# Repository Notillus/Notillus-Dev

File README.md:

Notillus
========

Repositorio de desarrollo de la Notillus, impresora originalmente inspirada en la Tantillus de https://github.com/Intrinsically-Sublime/Tantillus por su tamaño y portabilidad.

La Notillus ahora lleva el tanga extruder de coleta http://www.thingiverse.com/thing:742584

Los archivos de desarrollo de la Tantillus-Mks ahora estan en: 
https://github.com/darkjavi/Tantillus-MKS

Usando git:

Instrucciones para linux:

-Instalar:

	sudo apt-get install git

-Configurar

	git config --global user.name "TuNombre"

	git config --global user.email "tu@email.com"

-Primer clonado del repo:

	cd carpeta/donde/quieres/descargar

	git clone https://github.com/darkjavi/Notillus.git

-Actualizando el repo:

	cd carpeta/del/repo

	git pull

-Despues de haber modificado cosas en los ficheros:

	cd carpeta/del/repo

	git add .       (añade todos los archivos nuevos)

	git commit -a	(se abrira una ventana en la que obligatoriamente hay que escribir algo sobre los cambios hechos)

	git push origin (manda los cambios de vuelta a github, pedira nombre de usuario/pass)

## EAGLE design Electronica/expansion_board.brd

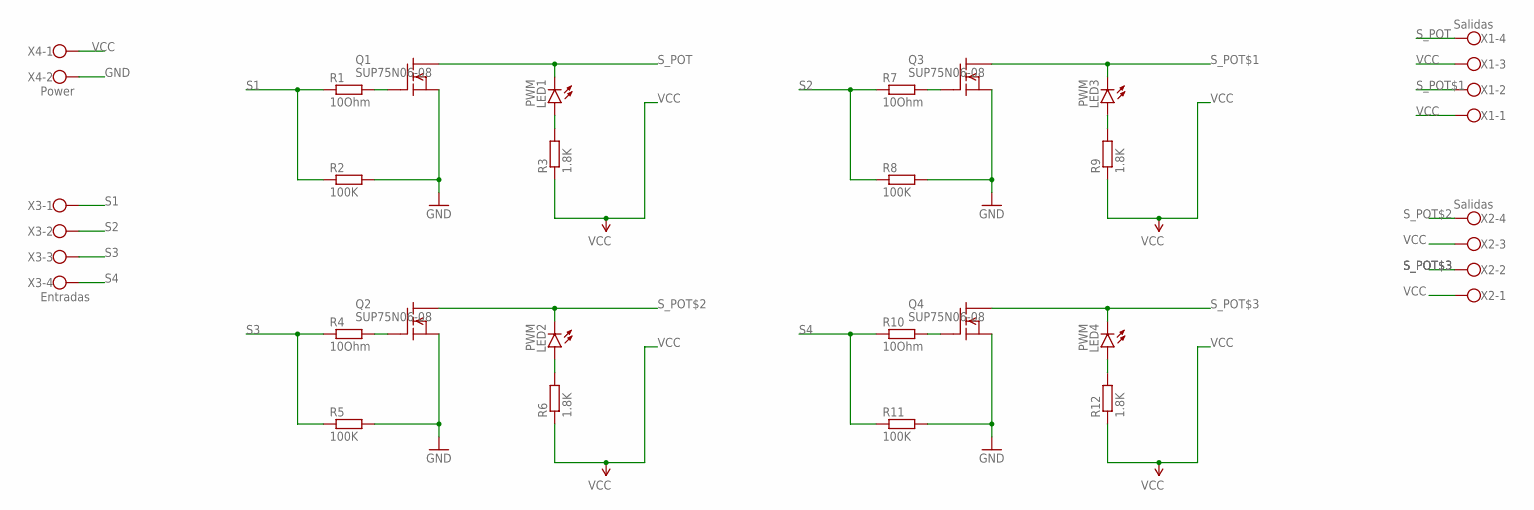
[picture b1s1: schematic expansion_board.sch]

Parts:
LED1, LED2, LED3, LED4: PWM; LED5MM
Q1, Q2, Q3, Q4: SUP75N06-08; TO220
R1, R4, R7, R10: 10Ohm; 0207/7
R2, R5, R8, R11: 100K; 0207/7
R3, R6, R9, R12: 1.8K; 0207/7
X1, X2: Salidas; W237-4
X3: Entradas; W237-4
X4: Power; W237-102

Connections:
GND: Q1.3 (S), Q2.3 (S), Q3.3 (S), Q4.3 (S), R2.2, R5.2, R8.2, R11.2, X4.2
unnamed: Q3.1 (G), R7.2
unnamed: Q1.1 (G), R1.2
unnamed: Q2.1 (G), R4.2
unnamed: LED1.A, R3.2
unnamed: LED2.A, R6.2
unnamed: LED3.A, R9.2
unnamed: Q4.1 (G), R10.2
unnamed: LED4.A, R12.2
S1: R1.1, R2.1, X3.1
S2: R7.1, R8.1, X3.2
S3: R4.1, R5.1, X3.3
S4: R10.1, R11.1, X3.4
S_POT: LED1.K (C), Q1.2 (D), X1.4
S_POT$1: LED3.K (C), Q3.2 (D), X1.2
S_POT$2: LED2.K (C), Q2.2 (D), X2.4
S_POT$3: LED4.K (C), Q4.2 (D), X2.2
VCC: R3.1, R6.1, R9.1, R12.1, X1.1, X1.3, X2.1, X2.3, X4.1

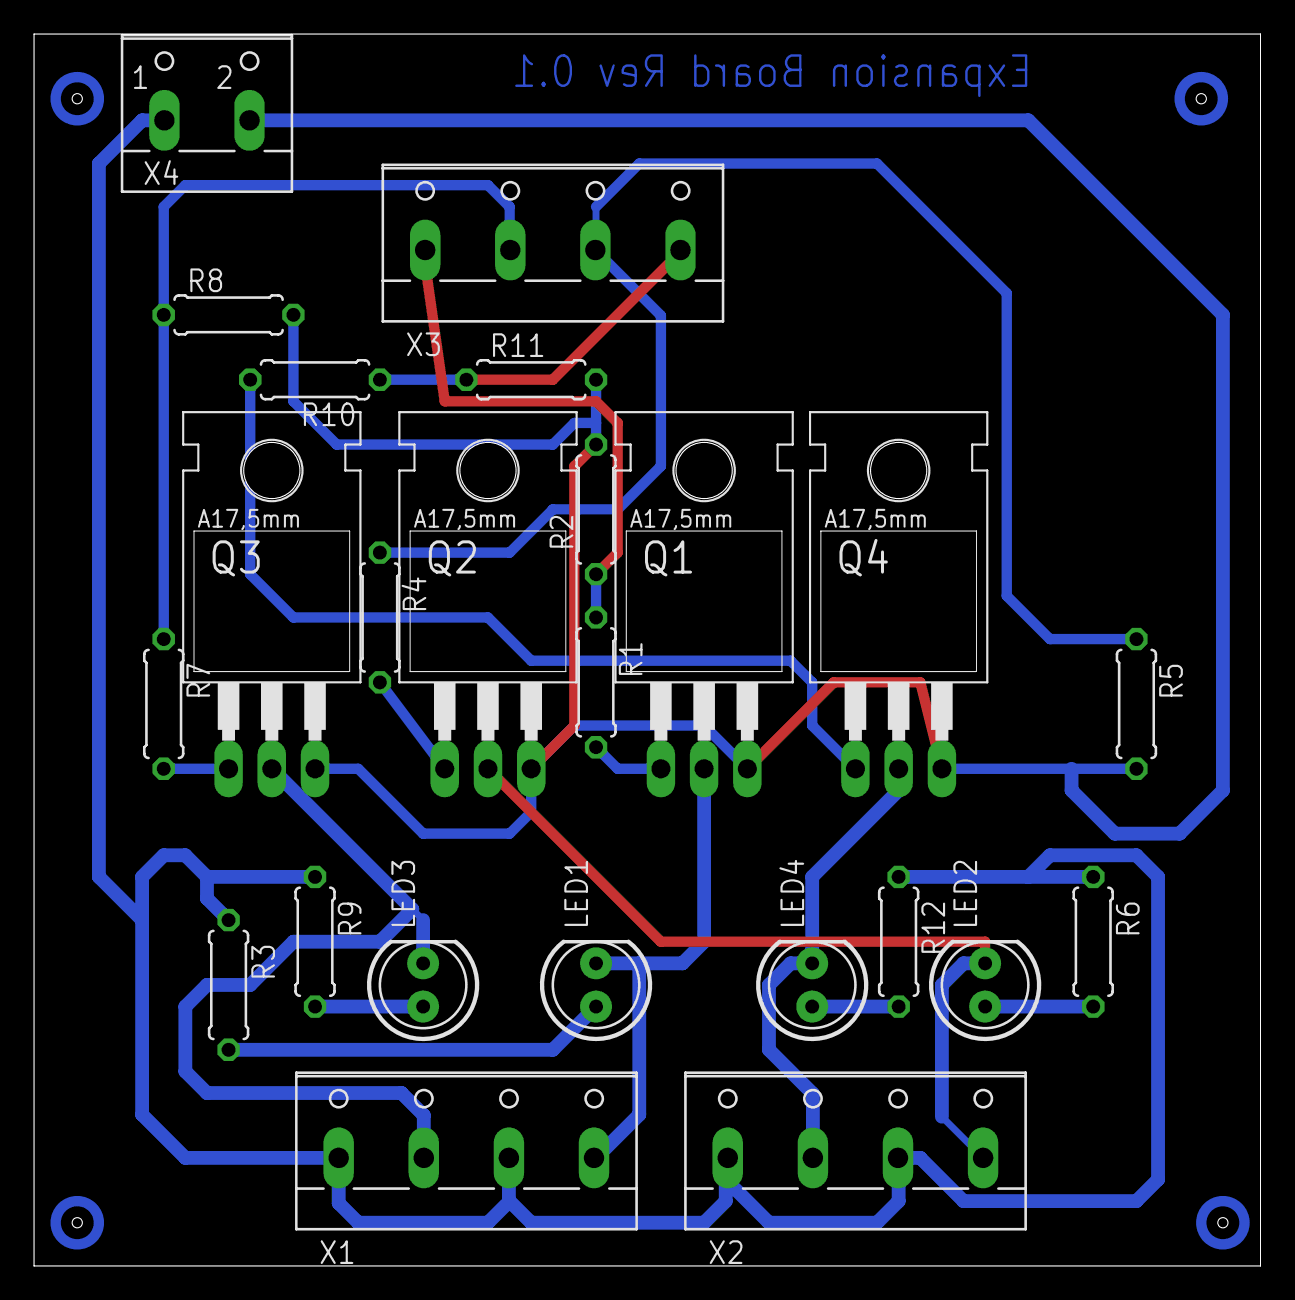
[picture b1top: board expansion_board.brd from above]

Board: 2 copper layers, 72.1 x 72.4 mm, 24 parts (0 on the bottom side), 18 nets.

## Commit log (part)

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2014-06-22 Añadida carpeta Electronica a Piezas Enrique y añadidas piezas caja electronica
2014-06-22 Creación carpeta EjeZ
2014-06-27 Primer commit. Añadidos todos los ficheros de mi portatil
2014-06-28 Añadidas instrucciones basicas para usar git desde la consola.
    Changes to be committed:
    modified: README.md
2014-06-28 Lista de piezas del eje Z
2014-06-29 modified: Notillus-coreXY/CorteLaser/LEEME.txt
2014-06-30 Versión alpha del chasis. Sin agujeros de anclaje ¡Las medidas del display hay que contrastarlas!
2014-07-24 Añadidos firmwares para tantillus original y version mks-moebyus
2014-07-31 Nuevo y mejorado barrilete para el hilo. 88 pasos por mm Firmware configurado para la version rslot de hilo con barilletes
    Changes to be committed:
    modified: Kit-TantillusMks-TSLOT/Extras/spectra-reel-m8-v2.stl
    modified: Kit-TantillusMks-TSLOT/Firmware/Marlin-tantillus-Moebyus/Marlin/Configuration.h
    modified: Piezas-Javi/Tantillus/spectra-reel-8mm-smaller2.fcstd
    renamed: Piezas-Javi/Tantillus/spectra-reel-8mm-smaller2.fcstd -> Piezas-Javi/Tantillus/spectra-reel-8mm-smaller2.fcstd1
2014-08-05 version 0.8 del soporte de filamento para la TSLOT new file: Piezas-Javi/Tantillus/soporte-filamento-pieza2.fcstd new file: Piezas-Javi/Tantillus/soporte-filamento-pieza2.fcstd1 new file: Piezas-Javi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
2014-08-08 Añadidos los soportes para los Nema de los ejes
2014-08-09 Empezados los esquinazos y las piezas de cruce del hilo
    new file: Piezas-Javi/Notillus/corexy-cruce-alineado.fcstd
    new file: Piezas-Javi/Notillus/esquina.fcstd
2014-08-11 Piezas del coreXY, falta ajustar la medida de las poleas del hilo
    new file: Piezas-Javi/Notillus/coreXY-carroY.fcstd
    new file: Piezas-Javi/Notillus/coreXY-frontal.fcstd
    new file: Piezas-Javi/Notillus/coreXY-trasera.fcstd
2014-08-12 Esquinas superioes listas para imprimir
2014-08-14 Reordenada la carpeta de Notillus
2014-08-16 new file: Notillus-coreXY/STL/esquinas-superiores.stl modified: Piezas-Javi/Notillus/esquina-superior.fcstd modified: Piezas-Javi/Notillus/esquina-superior.fcstd1 new file: Piezas-Javi/Notillus/esqui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
2014-08-16 Preliminar de la esquina inferior
    new file: Piezas-Javi/Notillus/esquina-inferior.fcstd
2014-08-16 Añadido frontal para el display Añadido rueda para el encoder del display Prototipo del cajon para electronica [¡COMPROBAR MEDIDAS!]
2014-08-16 Primera version de la pieza corexy-trasera. Imprime bien, aunque el final del carrera le queda un poco justo
    new file: Notillus-coreXY/XY/corexy-trasera.stl
2014-08-19 Modificada la ubicación del Slot SD
2014-08-19 ESquina inferior v1
2014-08-20 Nuevo molde para hacer las patas de silicona new file: Notillus-coreXY/Estructura/molde-patas.stl new file: Piezas-Javi/Tantillus/Molde-patas.fcstd
2014-08-21 carro x : pieza empezada soporte de motor achaflanado , tiempo estimado de impresion 1:45 new file: Piezas-Javi/Notillus/coreXY-carroX.fcstd new file: Piezas-Nano/soporte-Nema_v2-achaflanado.fcstd
2014-08-21 Modificada la guia de hilo
2014-08-22 Barrilete para el motor
2014-08-23 prototipo de tensor de hilo
2014-08-25 Barrilete optimizado para 100ppmm
2014-08-27 Soporte display adelgazado
2014-08-27 gcodes del display
2014-08-28 Barriletede hilo optimizado
2014-09-01 Mejora de los rieles del cajon
2014-09-02 Barriletes modificados Soporte para ventilador de capa Rieles de cajon [SIN MEDIDAS REALES]
2014-09-03 Nuevo Eje Z en progreso new file: Piezas-Javi/nuevo-z/plataforma.fcstd
2014-09-05 Cajon modificado [SIN TERMINAR]
2014-09-06 Enredando con el firmware para activar el ventilador de capa y cambiar el logo/textos de la pantalla de inicio. en add --all se han metido algunos ficheros antiguos que supongo que no se habian añadi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
2014-09-06 new file: Piezas-Javi/nuevo-z/z-completo-V2.fcstd
2014-09-06 Cajon de electronica 2.0
2014-09-07 Extrusor v0.8 new file: Piezas-Javi/Notillus/extrusor.fcstd
2014-09-07 añadido el extrusor al ensamblaje modified: Piezas-Javi/Notillus/Ensamblaje.fcstd
2014-09-07 Pequeños ajustes post-impresion modified: Notillus-coreXY/Extrusor/cuerpo-ext1.stl modified: Notillus-coreXY/Extrusor/cuerpo.stl modified: Piezas-Javi/Notillus/extrusor.fcstd
2014-09-08 Soporte motor Nema reducido
2014-09-10 Cajon de electronica achaflanado
2014-09-22 Trabajos en el eje Z modified: Piezas-Javi/nuevo-z/z-completo-V2.fcstd modified: Piezas-Javi/nuevo-z/z-completo-V2.fcstd1
2014-09-23 Tantillus mks: Invertido el Eje Y en el firmware, hay que invertir tambien el cable del motor
2014-09-26 Compartimento para repuestos y herramientas
2014-09-27 Soporte para imanes de 12mm
2014-09-27 Nuevo soporte para los motores
2014-09-27 Soportes para inclinar el Display
2014-09-29 Soporte motor rectificado.
2014-09-30 Soporte para filamento con tolerancias reparadas
2014-10-04 Idea de soporte de motor y doble barrilete para la traccion
    new file: Piezas-Javi/Notillus/soporte-motorv4.fcstd
2014-10-09 Mas trabajos en el Z modified: Piezas-Javi/nuevo-z/z-completo-V2.fcstd
2014-10-14 EjeZ 2.0 listo modified: Piezas-Javi/nuevo-z/z-completo-V2.fcstd modified: Piezas-Javi/nuevo-z/z-completo-V2.fcstd1
2014-10-15 new file: Piezas-Javi/Notillus/Carcasa/piezabase25x30.fcstd
2014-10-16 Avances en el soporte motor Nuevo ensamblaje para facilitar el diseño de la carcasa new file: Piezas-Javi/Notillus/Carcasa-Ensamblaje.fcstd modified: Piezas-Javi/Notillus/Carcasa/piezabase25x30.fcstd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
2014-10-21 Nueva esquina inferior un poco mas pequeña y con tornilleria M4 Agregada al ensamblaje modificado: Piezas-Javi/Notillus/Carcasa-Ensamblaje.fcstd new file: Piezas-Javi/Notillus/v2/esquina-inferior.fcs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
2014-10-22 new file: Notillus-coreXY/MotoresXY/barriteleV5.stl modificado: Piezas-Javi/Notillus/Carcasa-Ensamblaje.fcstd
2014-10-26 Nuevo trinquete para tensar el hilo en el carro. modified: Piezas-Javi/Notillus/v2/coreXY2.fcstd new file: Piezas-Javi/Notillus/v2/knob-trinquete.fcstd
2014-10-27 modified: Piezas-Javi/Notillus/v2/coreXY2.fcstd
2014-11-01 Version 2 del Compartimento de herramientas
2014-11-03 Soporte motor completado new file: Notillus-coreXY/MotoresXY/SoporteMotorV4.stl new file: Notillus-coreXY/MotoresXY/barriteleSecundarioV5.stl new file: Notillus-coreXY/MotoresXY/barriteleTractorV5.st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
2014-11-04 Cajón para la electronica
2014-11-05 Añadido el nuevo soporte display al ensamblaje modificado: Piezas-Javi/Notillus/Carcasa-Ensamblaje.fcstd
2014-11-13 Revisado enganche de cajon y display
2014-11-15 Barriletes 5.2 un poco mas grandes. Generados gcodes extralentos new file: Notillus-coreXY/MotoresXY/GCODE/barriteles-ABS-INSTAL-MEGATRON.gcode new file: Notillus-coreXY/MotoresXY/GCODE/barriteles-AB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
2014-11-29 new file: Notillus-coreXY/MotoresXY/barriteleSecundarioV5.2.stl new file: Notillus-coreXY/MotoresXY/barriteleTractorV5.2.stl modified: Piezas-Javi/Notillus/v2/coreXY2.fcstd modified: Piezas-Javi/Noti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
2014-11-30 Z retocado. Se acerca el conjunto a la pared 8mm para evitar colisiones con el hotend.
    modificado: Notillus-coreXY/Z2.0/z_idler.stl
    modificado: Notillus-coreXY/Z2.0/z_motor.stl
    modificado: Piezas-Javi/Notillus/Carcasa-Ensamblaje.fcstd
    modificado: Piezas-Javi/nuevo-z/z-completo-V2.fcstd
2014-11-30 Nuevo soporte motor y barrilete a juego. Añadidos al ensamblaje new file: Notillus-coreXY/MotoresXY/SoporteMotorV5-kiss.stl new file: Notillus-coreXY/MotoresXY/barrileteV6-kiss.stl modificado: Piezas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
2014-11-30 Cambio pines de extrusor E0
2014-11-30 Piezas xy listas para imprimir.
    reparada la maya del z_idler
    Limpieza general
    new file: Notillus-coreXY/XY/2xcorexy-frontal-1.1.stl
    new file: Notillus-coreXY/XY/2xcorexy-trasera-1.1.stl
    new file: Notillus-coreXY/XY/corexy-frontal-1.1.stl
    new file: Notillus-coreXY/XY/corexy-trasera-1.1.stl
2014-12-01 z_idler con la pestaña dada la vuelta.
    modificado: Piezas-Javi/Notillus/Ensamblaje1.1.fcstd
    modificado: Piezas-Javi/Notillus/Ensamblaje1.1.fcstd1
    modificado: Piezas-Javi/Z2.0/z-completo-V2.fcstd
    modificado: Piezas-Javi/Z2.0/z-completo-V2.fcstd1
2014-12-08 Nuevo y flamante soporte motor listo! He añadido los stls a la carpeta de motores xy, asi como los juegos de 2, que llevan la pieza y el correspondiente espejo de la misma. Tambien hay un STL de Cama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
    Cambios para hacer commit:
    new file: Notillus-coreXY/MotoresXY/2xBarrileteTractor.stl
    new file: Notillus-coreXY/MotoresXY/2xEngranajeMotor.stl
    new file: Notillus-coreXY/MotoresXY/2xsoporteMotorV6-VersionDM.stl
    new file: Notillus-coreXY/MotoresXY/Completo-GORT-PLA-3:30H.gcode
    modificado: Piezas-Javi/Notillus/Ensamblaje1.1.fcstd
2014-12-11 rectificados agujeros del Arduino
2014-12-23 Soporte para la fuente de alimentacion (x4)
2015-01-08 new file: Notillus-coreXY/MotoresXY/v7/2xsoporteCompletoConEspejo.stl new file: Notillus-coreXY/MotoresXY/v7/BigGear.stl new file: Notillus-coreXY/MotoresXY/v7/smallGear.stl new file: Notillus-coreXY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
2015-01-11 Nuevo trinquete para el hilo y nuevo carro x. Casi listos para imprimir. modificado: Piezas-Javi/Notillus/v1.1/coreXY1.1.fcstd modificado: Piezas-Javi/Notillus/v1.1/trinquete.fcstd
2015-01-17 Dos versiones de botiquin: - Nuevo soporte - Version no invasiva
2015-03-04 Borrador de Carcasa
2015-03-10 ficheros dxf reparados
2015-03-22 Trabajos en la carcasa, -sujecciones de las esquinas, -Agujeros frontales para acceso y para el cajon. -Añadida puerta lateral con bisagra para mejor acceso.
    frontal y laterales casi listos a falta de los agujeros de los motores y posicion final del cajon del display/electronica
    new file: Notillus-coreXY/Carcasa/Puerta-Ventis/bisagra.stl
    new file: Notillus-coreXY/Carcasa/Puerta-Ventis/cierre.stl
    new file: Notillus-coreXY/Carcasa/Puerta-Ventis/puerta.stl
    modificado: Piezas-Javi/CoreXY1.1/coreXY1.2.fcstd
    modificado: Piezas-Javi/Ensamblaje1.1.fcstd
2015-03-22 Mas trabajos en el ensamblaje. -Traidas ultimas versiones del ejeZ y corexy modificado: Piezas-Javi/Ensamblaje1.1.fcstd
2015-03-26 Incluidos accesorios de montaje
2015-03-27 Ensamblaje con nocturnidad y alevosia. Soporte Tanga
2015-03-28 Ideas de panel de interruptores. modificado: Piezas-Javi/Ensamblaje1.1.fcstd new file: Piezas-Javi/Panel-interruptores.fcstd
2015-03-28 Nuevo botiquin
2015-03-28 Abierto el boton de parada del display
2015-03-29 Nuevo panel de interruptores frontal. Protector del ventilador. Limpiza del archivo de ensamblaje.
    new file: Notillus-coreXY/Carcasa/Panel-Interruptores/panel.stl
    new file: Notillus-coreXY/Carcasa/Puerta-Ventis/protector-ventis.stl
    modificado: Piezas-Javi/Ensamblaje1.1.fcstd
    new file: Piezas-Javi/tapas-laterales.fcstd
2015-03-29 Mas agujeros :)
    Falta:
    Agujeros de las correderas¿distancia?
    Agujeros del botiquin (como se ensambla?)
    Agujeros de los tangas
2015-03-30 Placa de expansion de electronica
2015-03-30 Subido el esquematico de la expansion board
2015-04-01 botiquin rectificado y mejorado
2015-04-02 Notillus 1.0-RC1
    Archivos para el corte laser, falta exportar la tapa trasera.
    new file: Notillus-coreXY/Carcasa/CorteLaser/Frontal.dxf
    new file: Notillus-coreXY/Carcasa/CorteLaser/lateral-drcha.dxf
    new file: Notillus-coreXY/Carcasa/CorteLaser/lateral-izq.dxf
    modificado: Piezas-Javi/Ensamblaje1.1.fcstd
2015-04-05 Nuevo soporte motor acorde a los agujeros de la carcasa
    -Retocados los agujeros de la carcasa, se vuelven a exportar los dxf.
    -Idea de Protector de las poleas para retener el hilo.
    modificado: Notillus-coreXY/Carcasa/CorteLaser/lateral-drcha.dxf
    modificado: Notillus-coreXY/Carcasa/CorteLaser/lateral-izq.dxf
    new file: Notillus-coreXY/MotoresXY/2xSoporteMotorV8-completo.stl
    new file: Notillus-coreXY/MotoresXY/soporteMotorV8-completo.stl
2015-04-08 añadidos modelos para corte laser en PDF
    Tambien parece que el commit ha querido ahora coger un firmware que estaba en la carperta pero no se habia sincronizado.
2015-04-09 Fichero con piezas para imprimir y sus tiempos estimados

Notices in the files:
parts and their libraries:
SparkFun-LED: Licensing: Creative Commons ShareAlike 4.0 International - https://creativecommons.org/licenses/by-sa/4.0
